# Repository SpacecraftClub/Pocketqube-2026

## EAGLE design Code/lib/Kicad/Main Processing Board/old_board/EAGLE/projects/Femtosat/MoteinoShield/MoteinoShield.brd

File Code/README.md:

# PocketQube Flight Code

This firmware collects sensor data, logs it to the SD card, and transmits telemetry over LoRa radio.

## Viewing Data

There are three output paths:

1. Serial monitor
   Set `PRINT_SENSOR_CSV` to `true` in `src/main.cpp`. The firmware will print one CSV row per second at `9600` baud.

2. SD card logs
   Sensor data is written to CSV files by `src/sensor_logger.cpp`. Each row contains the current exported values for every sensor task.

3. Radio telemetry
   `src/radio.cpp` sends a binary packet containing a 2-byte sequence number followed by all exported sensor floats in task order.

## Sensor Task Order

Radio telemetry and CSV column order both follow the `sensorTasks[]` array in `src/taskHandles.cpp`.

Current task order:

1. `MS5611_Task`
2. `MMC5603_Task`
3. `LMSModule_Task`
4. `DS2782_BatteryMonitor_Task` when `POWER_MONITOR` is enabled

## Telemetry Field Order

### Base 12-float telemetry layout

If the battery monitor is not included in the radio payload, the 12 floats are:

1. `Pressure`
2. `Temp (MS5611)`
3. `x_mag`
4. `y_mag`
5. `z_mag`
6. `accel_x`
7. `accel_y`
8. `accel_z`
9. `gyro_x`
10. `gyro_y`
11. `gyro_z`
12. `temp_LMS`

Example:

`Telemetry: SEQ=9 Floats(12): 84966.555 23.303 913.164 1053.115 592.743 -0.002 0.120 1.024 -0.366 0.149 -0.549 20.222`

This maps to:

1. `84966.555` = `Pressure`
2. `23.303` = `Temp (MS5611)`
3. `913.164` = `x_mag`
4. `1053.115` = `y_mag`
5. `592.743` = `z_mag`
6. `-0.002` = `accel_x`
7. `0.120` = `accel_y`
8. `1.024` = `accel_z`
9. `-0.366` = `gyro_x`
10. `0.149` = `gyro_y`
11. `-0.549` = `gyro_z`
12. `20.222` = `temp_LMS`

### Battery monitor fields

When `POWER_MONITOR` is enabled, the DS2782 task adds these fields after `temp_LMS`:

13. `batt_voltage`
14. `batt_current`
15. `batt_power`
16. `batt_energy`
17. `batt_capacity`
18. `batt_soc`

## Likely Units

1. `Pressure`: Pa
2. `Temp (MS5611)`: C
3. `x_mag`, `y_mag`, `z_mag`: uT
4. `accel_x`, `accel_y`, `accel_z`: g
5. `gyro_x`, `gyro_y`, `gyro_z`: deg/s
6. `temp_LMS`: C
7. `batt_voltage`: V
8. `batt_current`: A
9. `batt_power`: W
10. `batt_energy`: J
11. `batt_capacity`: mAh
12. `batt_soc`: percent

## Important Radio Note

`src/radio.cpp` now computes the telemetry payload length from the enabled sensor tasks and checks it against `MAX_TELEMETRY_PACKET_LEN = 96`.

That is enough for the current telemetry set:

1. `2` bytes of sequence number
2. `18` floats = `72` bytes
3. Total `74` bytes

If more sensor fields are added later and the payload grows past `96` bytes, radio initialization will fail until the limit is increased.

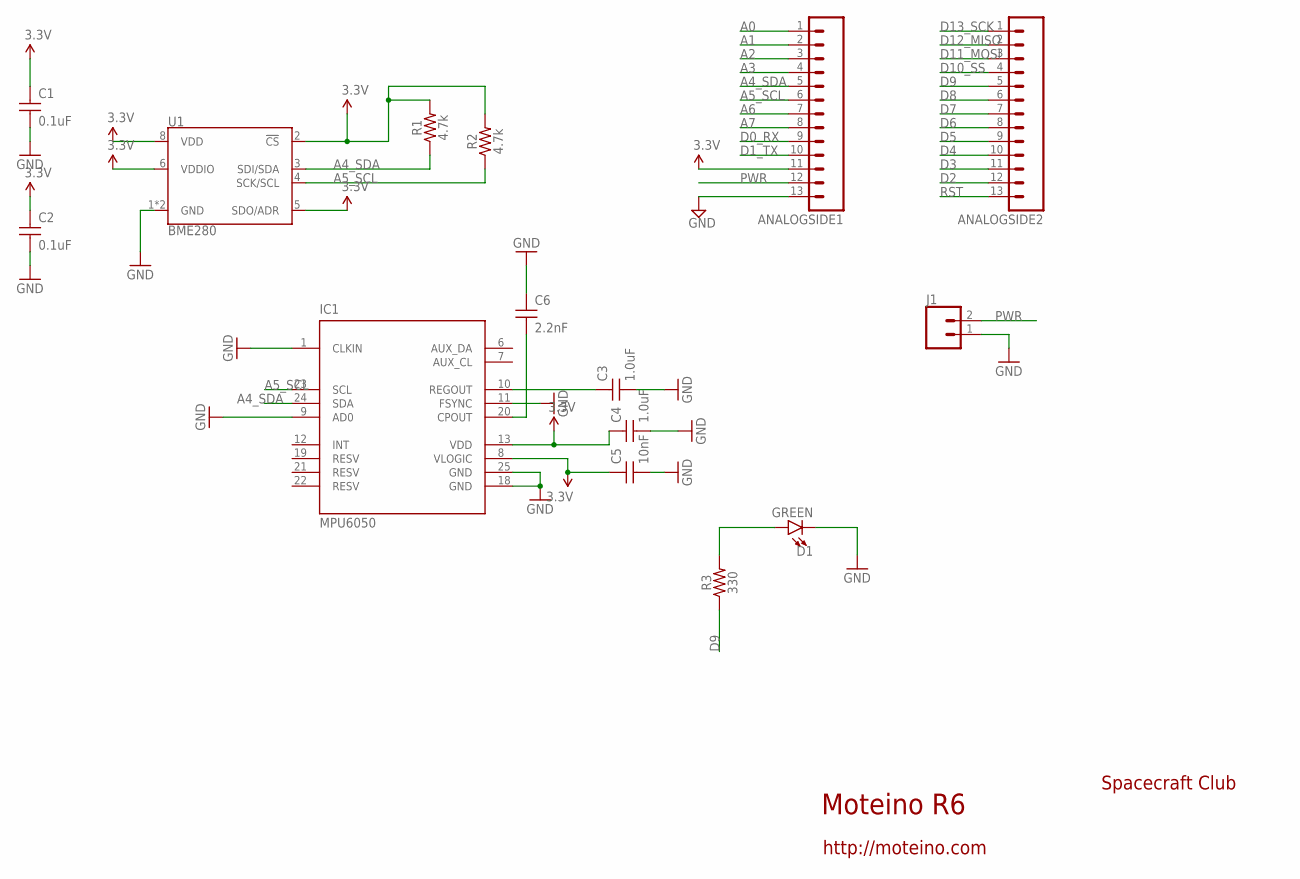
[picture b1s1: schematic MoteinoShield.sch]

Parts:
ANALOGSIDE1, ANALOGSIDE2: HDR_13PINTHIN_RINGS; 1X13_THINRINGS
C1, C2: 0.1uF; 0603-CAP
C3, C4: 1.0uF; 0603
C5: 10nF; 0603
C6: 2.2nF; 0603
D1: GREEN; LED-0603
IC1: MPU6050; QFN50P400X400X95-25T265X275N
J1: CONNECTOR_2PINJST-PTH-2; JST-2-PTH
R1, R2: 4.7k; 0603
R3: 330; 0603
U1: BME280; LGA-8-2.5X2.5

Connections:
3.3V: C1.1, C2.1, C4.1, C5.1, IC1.8 (VLOGIC), IC1.13 (VDD), R1.2, R2.2, U1.2 (!CS), U1.5 (SDO/ADR), U1.6 (VDDIO), U1.8 (VDD)
A0: ANALOGSIDE1.1
A1: ANALOGSIDE1.2
A2: ANALOGSIDE1.3
A3: ANALOGSIDE1.4
A4_SDA: ANALOGSIDE1.5, IC1.24 (SDA), R1.1, U1.3 (SDI/SDA)
A5_SCL: ANALOGSIDE1.6, IC1.23 (SCL), R2.1, U1.4 (SCK/SCL)
A6: ANALOGSIDE1.7
A7: ANALOGSIDE1.8
D0_RX: ANALOGSIDE1.9
D1_TX: ANALOGSIDE1.10
D2: ANALOGSIDE2.12
D3: ANALOGSIDE2.11
D4: ANALOGSIDE2.10
D5: ANALOGSIDE2.9
D6: ANALOGSIDE2.8
D7: ANALOGSIDE2.7
D8: ANALOGSIDE2.6
D9: ANALOGSIDE2.5, R3.1
D10_SS: ANALOGSIDE2.4
D11_MOSI: ANALOGSIDE2.3
D12_MISO: ANALOGSIDE2.2
D13_SCK: ANALOGSIDE2.1
GND: ANALOGSIDE1.13, C1.2, C2.2, C3.2, C4.2, C5.2, C6.1, D1.C, IC1.1 (CLKIN), IC1.9 (AD0), IC1.11 (FSYNC), IC1.18 (GND), IC1.25 (GND), J1.1 (2), U1.1 (GND), U1.7 (GND)
unnamed: D1.A, R3.2
unnamed: C3.1, IC1.10 (REGOUT)
unnamed: C6.2, IC1.20 (CPOUT)
PWR: ANALOGSIDE1.12, J1.2 (1)
RST: ANALOGSIDE2.13
VCC: ANALOGSIDE1.11

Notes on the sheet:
Moteino R6
Spacecraft Club
http://moteino.com

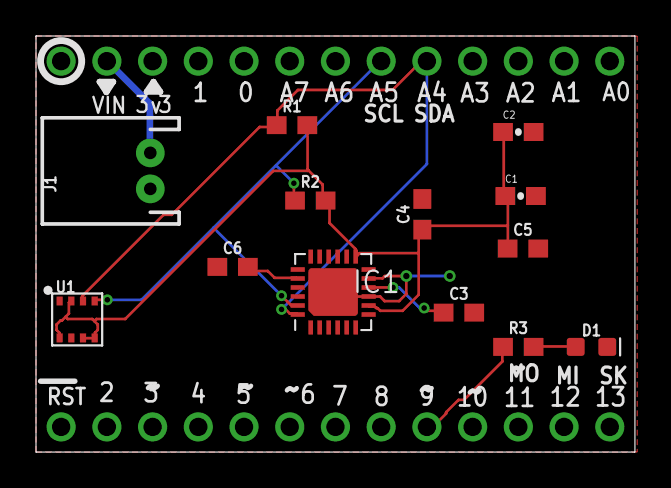
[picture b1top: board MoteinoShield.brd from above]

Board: 2 copper layers, 33.3 x 23.1 mm, 15 parts (0 on the bottom side), 9 nets.

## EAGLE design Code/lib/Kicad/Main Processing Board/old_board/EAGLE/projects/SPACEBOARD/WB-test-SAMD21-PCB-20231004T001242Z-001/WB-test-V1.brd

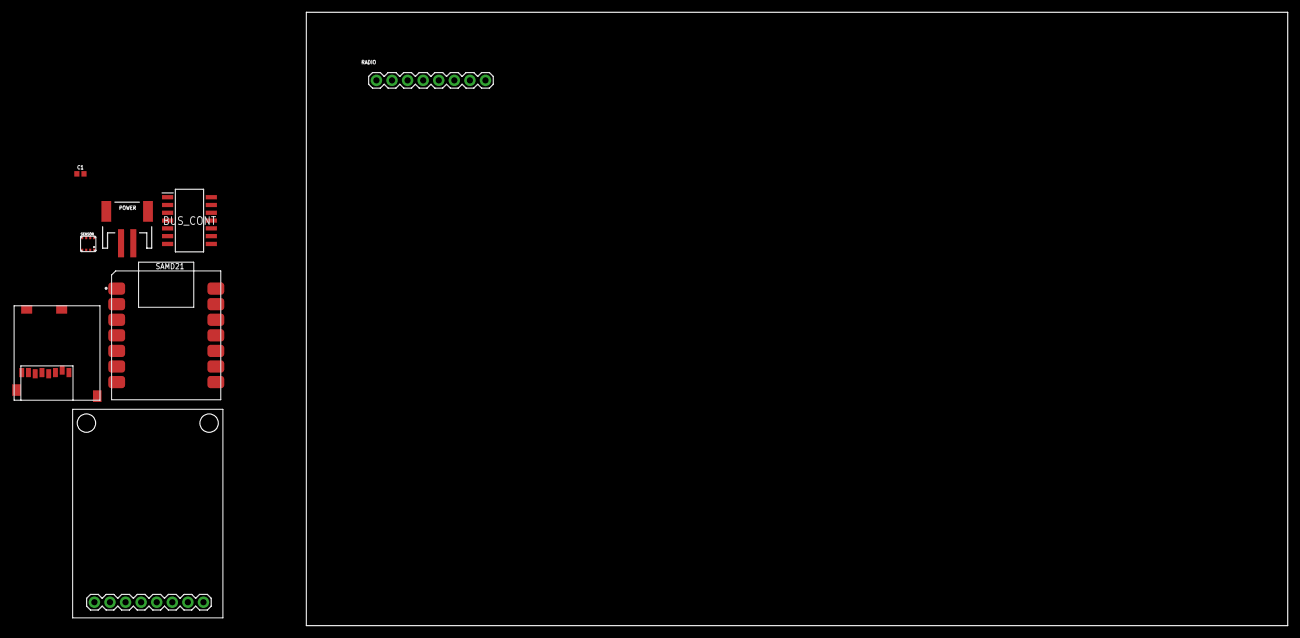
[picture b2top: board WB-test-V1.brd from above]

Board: 2 copper layers, 160.0 x 100.0 mm, 8 parts (0 on the bottom side), 16 nets, no tracks yet.

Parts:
BUS_CONT: SOIC127P780X200-14N
C1: 0.1uF; 0402
CAM: ARDUCAM_MINI
POWER: JST-2-SMD
RADIO: 1X08
SAMD21: MOUDLE14P-2.54-21X17.8MM
SD: SD_READER; SDREAD
SENSOR: BME280

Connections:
3V3: BUS_CONT.14, C1.2, RADIO.8, SAMD21.12, SD.VDD, SENSOR.6, SENSOR.8
5V: POWER.2, RADIO.2, SAMD21.14
CS_BME: SAMD21.4, SENSOR.2
CS_CAM: CAM.CS, SAMD21.3
CS_RAD: BUS_CONT.10, BUS_CONT.13, RADIO.3, SAMD21.7
CS_SD: BUS_CONT.1, BUS_CONT.4, SAMD21.8, SD.CS
GND: BUS_CONT.7, C1.1, POWER.1, RADIO.1, RADIO.7, SAMD21.13, SENSOR.1, SENSOR.7
MISO: BUS_CONT.3, BUS_CONT.11, CAM.MISO, SAMD21.10, SENSOR.5
MISO_RAD: BUS_CONT.12, RADIO.4
MISO_SD: BUS_CONT.2, SD.MISO
MOSI: BUS_CONT.5, BUS_CONT.9, CAM.MOSI, SAMD21.11, SENSOR.3
MOSI_RAD: BUS_CONT.8, RADIO.5
MOSI_SD: BUS_CONT.6, SD.MOSI
unnamed: CAM.SDA, SAMD21.5
unnamed: CAM.SCL, SAMD21.6
SCK: CAM.SCK, RADIO.6, SAMD21.9, SD.SCK, SENSOR.4

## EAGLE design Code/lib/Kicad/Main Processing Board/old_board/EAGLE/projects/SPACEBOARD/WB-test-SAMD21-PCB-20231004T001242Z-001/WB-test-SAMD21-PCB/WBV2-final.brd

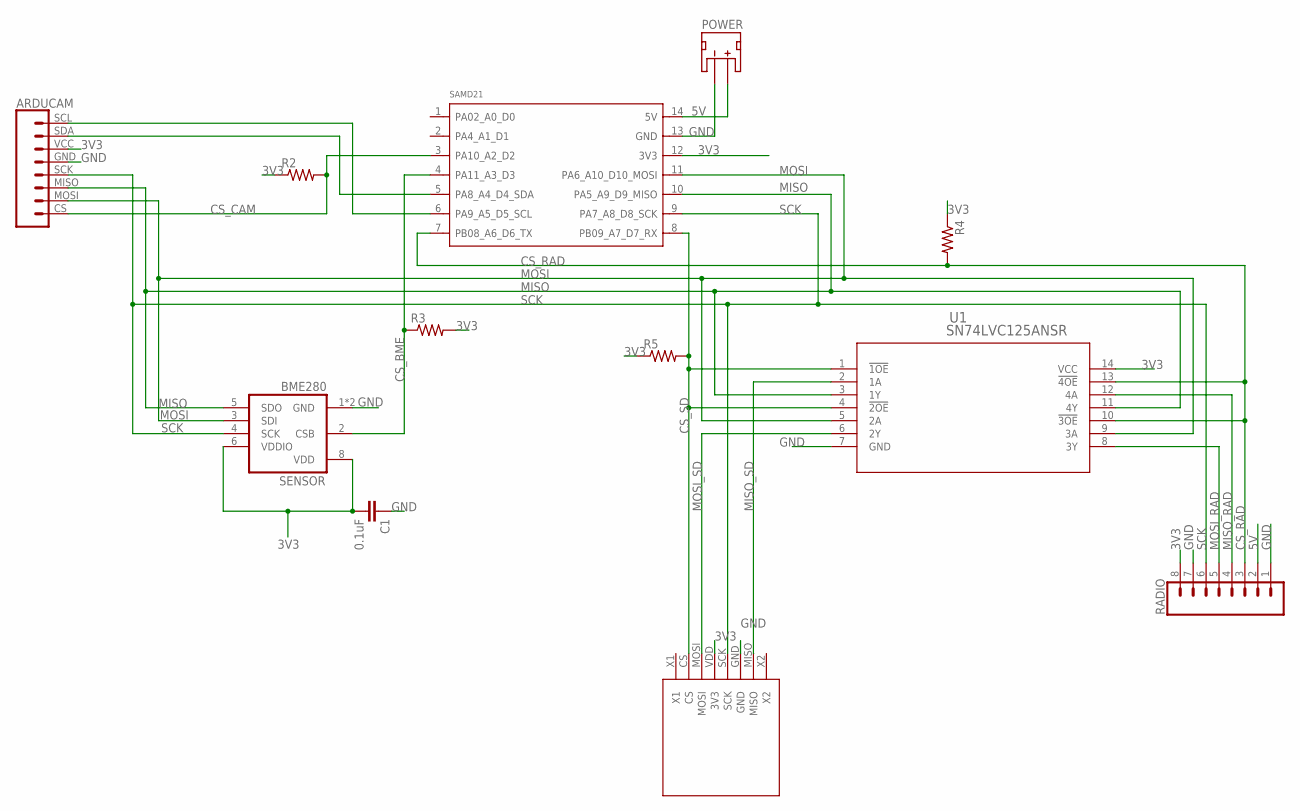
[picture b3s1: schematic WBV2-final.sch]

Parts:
C1: 0.1uF; 0402
CAM: ARDUCAM_MINI
POWER: JST_2MM_MALE; JST-2-SMD
R2, R3, R4, R5: R-US_R0402; R0402
RADIO: CONN_08"; 1X08
SAMD21: MOUDLE-SEEEDUINO-XIAO; MOUDLE14P-2.54-21X17.8MM
SD: SD_READER; SDREAD
SENSOR: BME280
U1: SN74LVC125ANSR; NS14

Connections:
3V3: C1.2, CAM.VCC, R2.1, R3.2, R4.1, R5.1, RADIO.8, SAMD21.12 (3V3), SD.VDD (3V3), SENSOR.6 (VDDIO), SENSOR.8 (VDD), U1.14 (VCC)
5V: POWER.2 (+), RADIO.2, SAMD21.14 (5V)
CS_BME: R3.1, SAMD21.4 (PA11_A3_D3), SENSOR.2 (CSB)
CS_CAM: CAM.CS, R2.2, SAMD21.3 (PA10_A2_D2)
CS_RAD: R4.2, RADIO.3, SAMD21.7 (PB08_A6_D6_TX), U1.10 (!3OE), U1.13 (!4OE)
CS_SD: R5.2, SAMD21.8 (PB09_A7_D7_RX), SD.CS, U1.1 (!1OE), U1.4 (!2OE)
GND: C1.1, CAM.GND, POWER.1 (-), RADIO.1, RADIO.7, SAMD21.13 (GND), SD.GND, SENSOR.1 (GND), SENSOR.7 (GND), U1.7 (GND)
MISO: CAM.MISO, SAMD21.10 (PA5_A9_D9_MISO), SENSOR.5 (SDO), U1.3 (1Y), U1.11 (4Y)
MISO_RAD: RADIO.4, U1.12 (4A)
MISO_SD: SD.MISO, U1.2 (1A)
MOSI: CAM.MOSI, SAMD21.11 (PA6_A10_D10_MOSI), SENSOR.3 (SDI), U1.5 (2A), U1.9 (3A)
MOSI_RAD: RADIO.5, U1.8 (3Y)
MOSI_SD: SD.MOSI, U1.6 (2Y)
unnamed: CAM.SDA, SAMD21.5 (PA8_A4_D4_SDA)
unnamed: CAM.SCL, SAMD21.6 (PA9_A5_D5_SCL)
SCK: CAM.SCK, RADIO.6, SAMD21.9 (PA7_A8_D8_SCK), SD.SCK, SENSOR.4 (SCK)

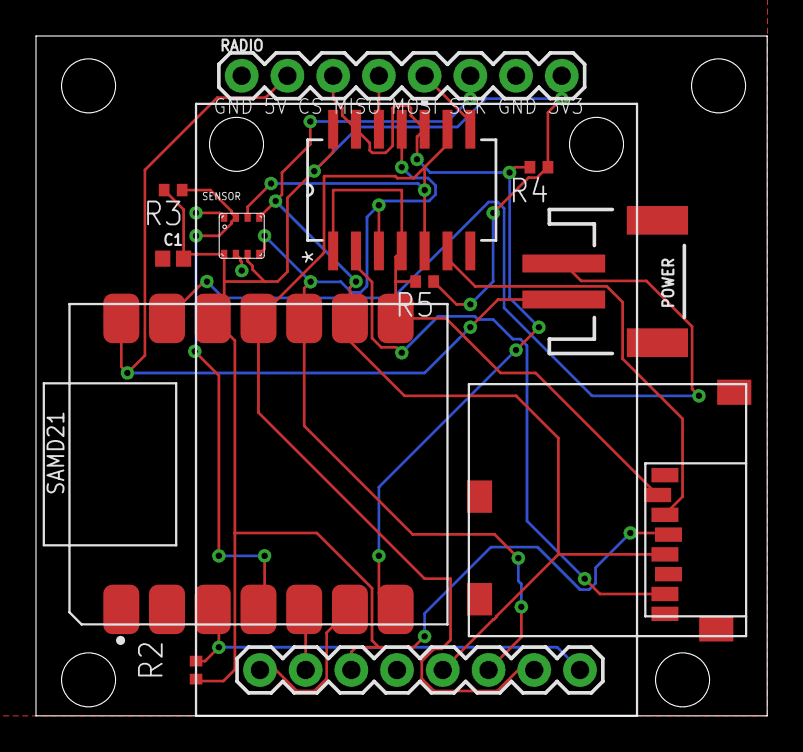
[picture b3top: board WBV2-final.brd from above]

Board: 2 copper layers, 40.6 x 37.8 mm, 12 parts (0 on the bottom side), 16 nets.

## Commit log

2025-09-24 started routing
    added ground plane
2025-09-24 more routing
    I worked on the routing some more, focusing mostly on the bottom right corner. I still need to change the thickness of the connections I made to 0.5
2025-10-01 added altium files
2025-10-01 added more altium files
2025-10-01 more routing
    I did some more routing. Will likely have to redo part of it, as I'm getting stuck
2025-10-07 more routing
    Did as much as I could but got stuck so will need to redo some parts.
2025-10-08 Finished PCB Routing
    There were some merge conflicts, so if something seems off, then it probably is.
2025-10-15 edited connection widths
2025-10-29 added BOM work
2025-11-05 updated 3d model
2025-11-26 Updated code
    Code now works with current hardware
2026-01-28 Added Test code for camera
2026-01-28 Updated code to verify UHD camera
2026-01-29 started creating stats.cpp
    - added unit tests as well
2026-02-02 Finished Preliminary Stats Library
    - Now you can calculate the mean of a dataset (without outliers)
    - Added Unit Tests to verify functionality of the library
2026-02-03 Updated Scheduler
    Set ground work so that we can begin making the new sensor platform
    - New task based scheduler for modularity
    - Cleaned code to make it more readable & configurable
2026-02-03 Added some stats errors prevention
2026-02-11 MMC5603 sensor code
    Wrote code for MMC5603 sensor. It compiles
2026-02-18 Camera now works and is more stable
2026-02-25 LMS Module files
    Wrote .h and .cpp files for the LMS Module functions
2026-03-04 Added sensor logger header file
2026-03-04 Created sensor_logger.cpp
    Implemented initializer
2026-03-11 Resolved Stats Error
2026-03-11 adjusted prints to only print when debugging
2026-03-11 Updated Stats Tests
    Now it tests calculated means of raw data.
2026-03-25 Updated sensor_logger.cpp
2026-03-26 working logging code
2026-04-23 radio code
2026-04-24 updated radio parameters
2026-04-25 updated radio and power monitor code
2026-04-25 removed power monitor code
2026-04-28 Added 3d Models
    + print profiles

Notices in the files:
parts and their libraries:
SparkFun-Capacitors: Licensing: Creative Commons ShareAlike 4.0 International - https://creativecommons.org/licenses/by-sa/4.0
COPYRIGHT: Copyright (C) 2024 Ultra Librarian. All rights reserved.
